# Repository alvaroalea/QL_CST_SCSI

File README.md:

# CST SCSI/FLOPPY CONTROLLER for Sinclar QL

A clone of the CST's Floppy + hardisc Interface for the Sinclair QL

# WARNING: DO NOT USE THIS PROJECT IS NOT TESTED AND MISSING THINGS

An evolution of the CST V4 Floppy interface with the incorporation of SCSI Controller.

The SCSI was limited only to a especific HDD model: Rodine RO652 20Mb, an UK Manufactured HDD that was also used on Macintosh SE

Later this interface will be use as a base for the Thor 20 Computer SCSI interface.

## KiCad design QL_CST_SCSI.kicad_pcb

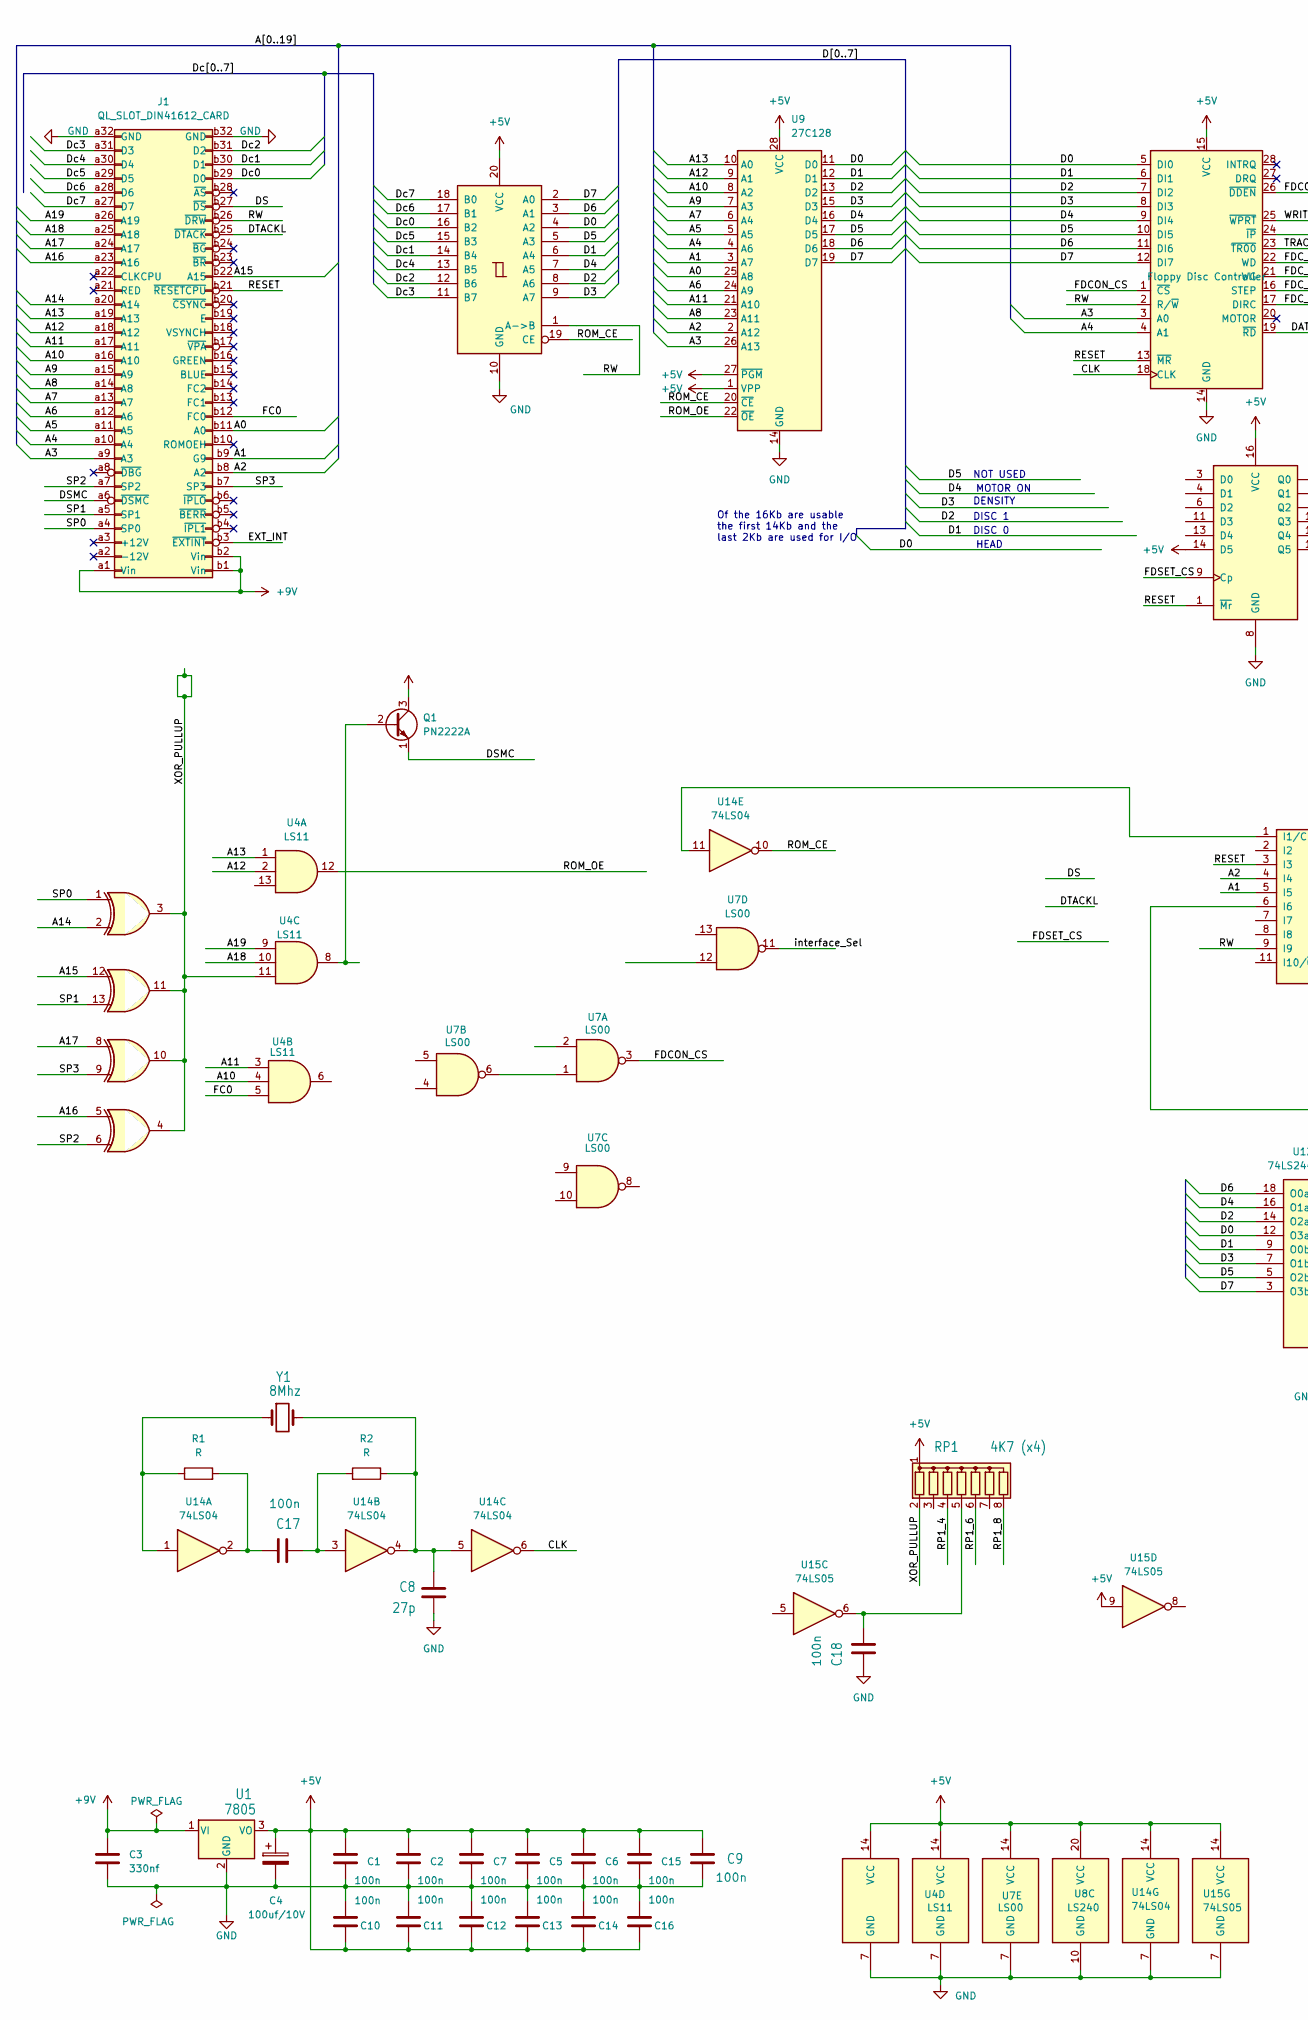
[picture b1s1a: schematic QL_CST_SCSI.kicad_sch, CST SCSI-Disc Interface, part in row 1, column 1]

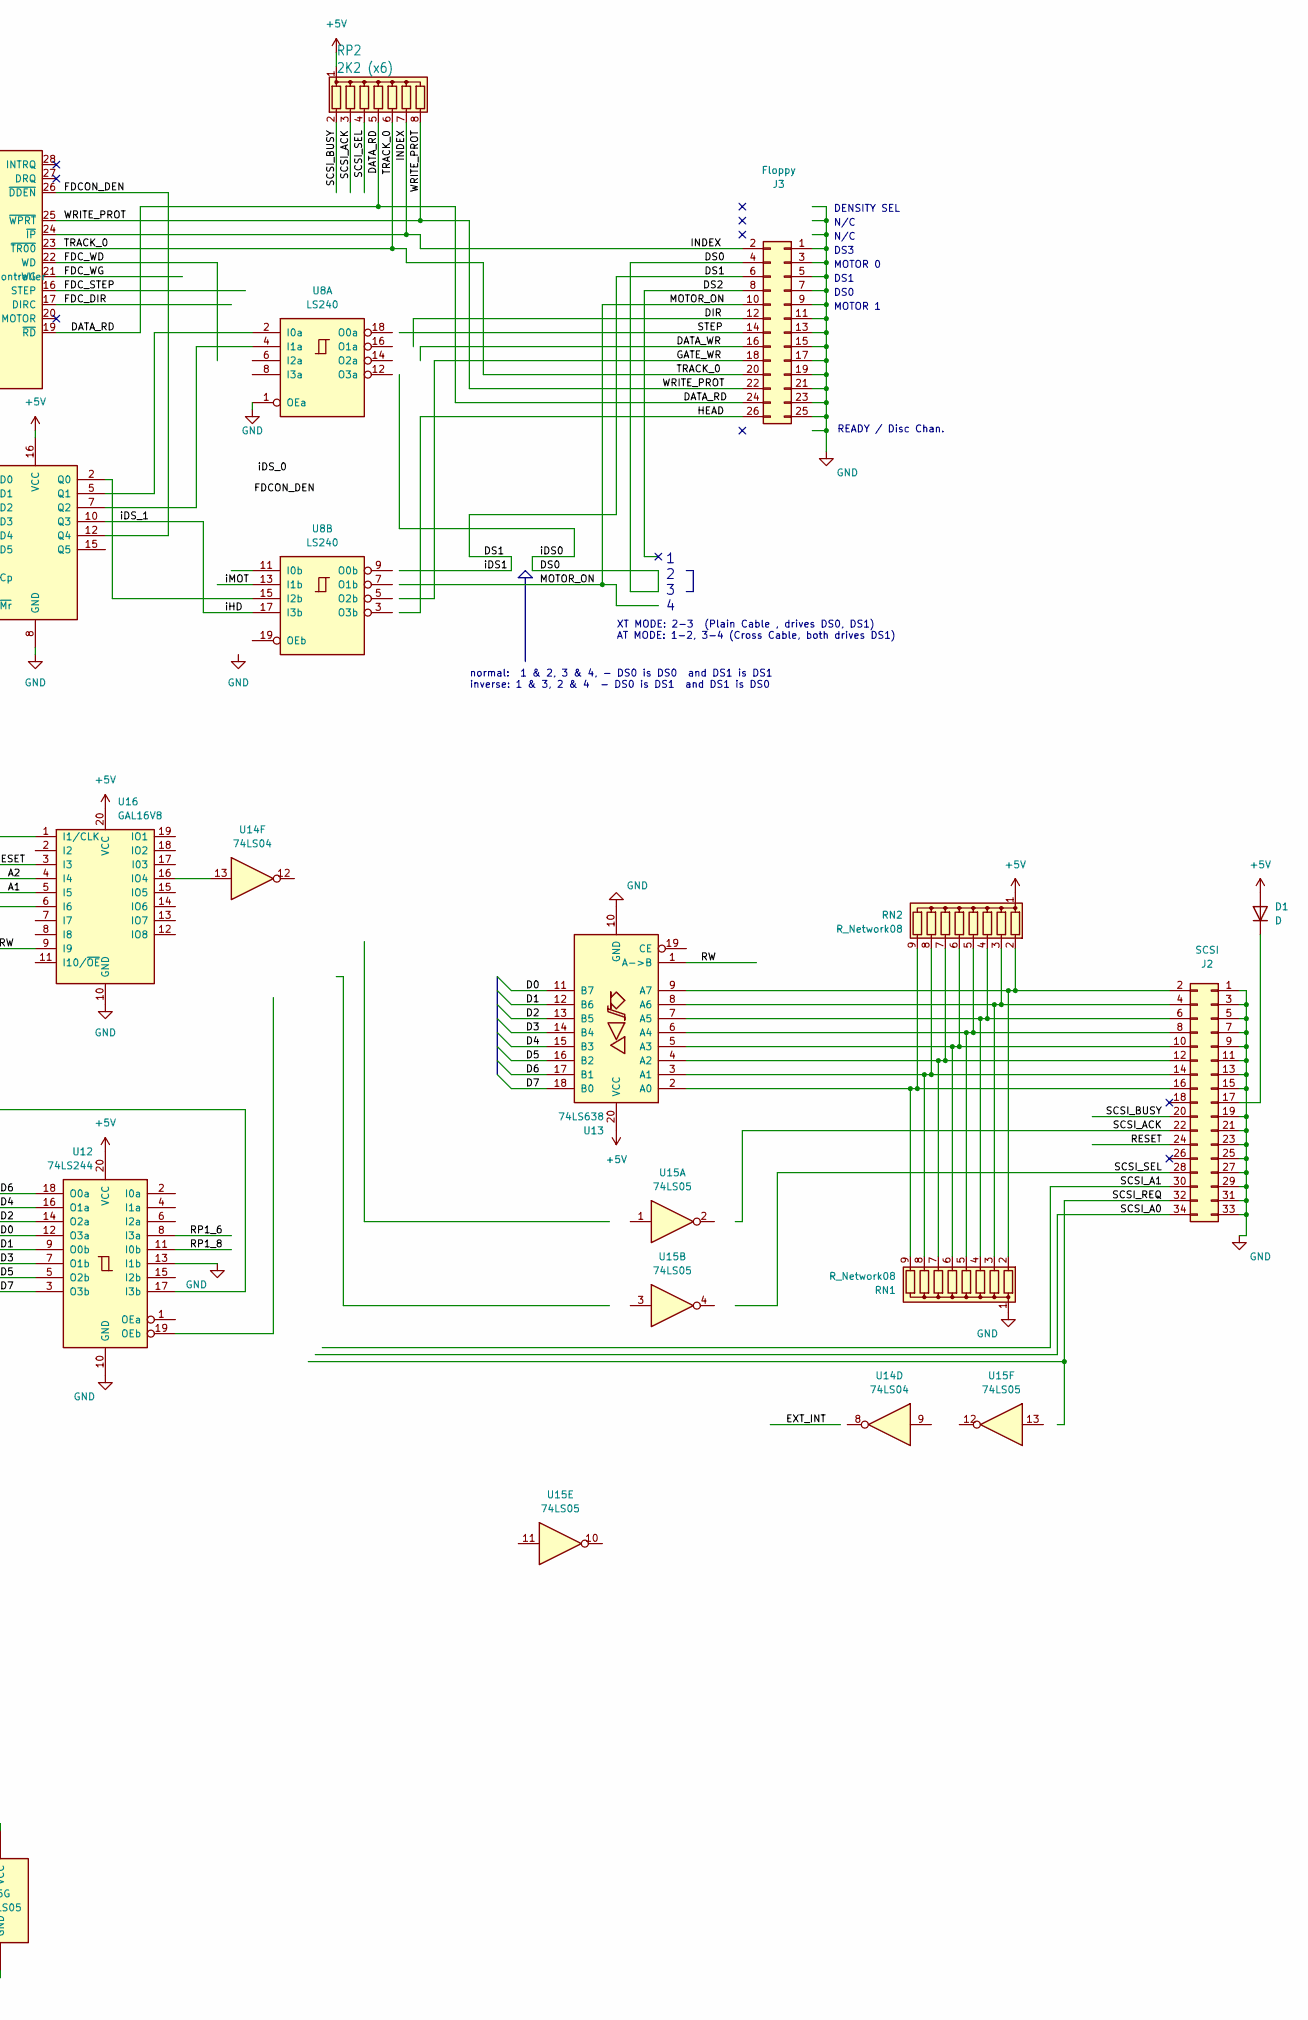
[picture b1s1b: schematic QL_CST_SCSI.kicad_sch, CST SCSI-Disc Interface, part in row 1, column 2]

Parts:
C1, C2, C5, C6, C7, C9, C10, C11, C12, C13, C14, C15, C16, C17, C18: 100n; C_Disc_D7.0mm_W2.5mm_P5.00mm
C3: 330nf; C_Disc_D7.0mm_W2.5mm_P5.00mm
C4: 100uf/10V; CP_Radial_D5.0mm_P2.50mm
C8: 27p; C_Disc_D7.0mm_W2.5mm_P5.00mm
D1: D; D_DO-34_SOD68_P7.62mm_Horizontal
J1: QL_SLOT_DIN41612_CARD; DIN41612_B_2x32_Female_Horizontal_THT
J2: SCSI; PinHeader_2x17_P2.54mm_Vertical
J3: Floppy; PinHeader_2x13_P2.54mm_Vertical
Q1: PN2222A; TO-92S_Wide
R1, R2: R; R_Axial_DIN0207_L6.3mm_D2.5mm_P10.16mm_Horizontal
RN1, RN2: R_Network08; R_Array_SIP9
RP1: 4K7 (x4); R_Array_SIP8
RP2: 2K2 (x6); R_Array_SIP8
U1: 7805; TO-220-3_Horizontal_TabDown
U2: LS266; DIP-14_W7.62mm_Socket
U4: LS11; DIP-14_W7.62mm_Socket
U5: LS245; DIP-20_W7.62mm_Socket
U7: LS00; DIP-14_W7.62mm_Socket
U8: LS240; DIP-20_W7.62mm_Socket
U9: 27C128; DIP-28_W15.24mm_Socket
U10: WD1770; DIP-28_W15.24mm_Socket
U11: LS174; DIP-16_W7.62mm_Socket
U12: 74LS244; DIP-20_W7.62mm_Socket
U13: 74LS638; DIP-20_W7.62mm_Socket
U14: 74LS04; DIP-14_W7.62mm_Socket
U15: 74LS05; DIP-14_W7.62mm_Socket
U16: GAL16V8; DIP-20_W7.62mm_Socket
Y1: 8Mhz; Crystal_HC18-U_Horizontal

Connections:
+5V: C1.1, C2.1, C4.1, C5.1, C6.1, C7.1, C9.2, C10.1, C11.1, C12.1, C13.1, C14.1, C15.1, C16.1, D1.2 (A), Q1.3 (C), RN2.1 (common), RP1.1 (common), RP2.1 (common), U1.3 (VO), U2.14 (VCC), U4.14 (VCC), U5.20 (VCC), U7.14 (VCC), U8.20 (VCC), U9.1 (VPP), U9.27 (~PGM), U9.28 (VCC), U10.15 (VCC), U11.14 (D5), U11.16 (VCC), U12.20 (VCC), U13.20 (VCC), U14.14 (VCC), U15.9, U15.14 (VCC), U16.20 (VCC)
+9V: C3.1, J1.a1 (Vin), J1.b1 (Vin), J1.b2 (Vin), U1.1 (VI)
/A0: J1.b11 (A0), U9.25 (A8)
/A1: J1.b9 (G9), U9.3 (A7), U16.5 (I5)
/A2: J1.b8 (A2), U9.2 (A12), U16.4 (I4)
/A3: J1.a9 (A3), U9.26 (A13), U10.3 (A0)
/A4: J1.a10 (A4), U9.4 (A6), U10.4 (A1)
/A5: J1.a11 (A5), U9.5 (A5)
/A6: J1.a12 (A6), U9.24 (A9)
/A7: J1.a13 (A7), U9.6 (A4)
/A8: J1.a14 (A8), U9.23 (A11)
/A9: J1.a15 (A9), U9.7 (A3)
/A10: J1.a16 (A10), U4.4, U9.8 (A2)
/A11: J1.a17 (A11), U4.3, U9.21 (A10)
/A12: J1.a18 (A12), U4.2, U9.9 (A1)
/A13: J1.a19 (A13), U4.1, U9.10 (A0)
/A14: J1.a20 (A14), U2.2
/A15: J1.b22 (A15), U2.12
/A16: J1.a23 (A16), U2.5
/A17: J1.a24 (A17), U2.8
/A18: J1.a25 (A18), U4.10
/A19: J1.a26 (A19), U4.9
/CLK: U10.18 (CLK), U14.6
/D0: U5.4 (A2), U9.11 (D0), U10.5 (DI0), U12.12 (O3a), U13.11 (B7)
/D1: U5.6 (A4), U9.12 (D1), U10.6 (DI1), U12.9 (O0b), U13.12 (B6)
/D2: U5.8 (A6), U9.13 (D2), U10.7 (DI2), U12.14 (O2a), U13.13 (B5)
/D3: U5.9 (A7), U9.15 (D3), U10.8 (DI3), U12.7 (O1b), U13.14 (B4)
/D4: U5.7 (A5), U9.16 (D4), U10.9 (DI4), U12.16 (O1a), U13.15 (B3)
/D5: U5.5 (A3), U9.17 (D5), U10.10 (DI5), U12.5 (O2b), U13.16 (B2)
/D6: U5.3 (A1), U9.18 (D6), U10.11 (DI6), U12.18 (O0a), U13.17 (B1)
/D7: U5.2 (A0), U9.19 (D7), U10.12 (DI7), U12.3 (O3b), U13.18 (B0)
/DATA_RD: J3.24, RP2.5 (R4), U10.19 (~RD)
/DATA_WR: J3.16
/DIR: J3.12
/DS: J1.b27 (~DS)
/DS0: J3.4
/DS1: J3.6
/DS2: J3.8
/DSMC: J1.a6 (~DSMC), Q1.1 (E)
/DTACKL: J1.b25 (~DTACK)
/Dc0: J1.b29 (D0), U5.16 (B2)
/Dc1: J1.b30 (D1), U5.14 (B4)
/Dc2: J1.b31 (D2), U5.12 (B6)
/Dc3: J1.a31 (D3), U5.11 (B7)
/Dc4: J1.a30 (D4), U5.13 (B5)
/Dc5: J1.a29 (D5), U5.15 (B3)
/Dc6: J1.a28 (D6), U5.17 (B1)
/Dc7: J1.a27 (D7), U5.18 (B0)
/EXT_INT: J1.b3 (~EXTINT)
/FC0: J1.b12 (FC0), U4.5
/FDCON_CS: U7.3, U10.1 (~CS)
/FDCON_DEN: U10.26 (~DDEN), U11.12 (Q4)
/FDC_DIR: U10.17 (DIRC)
/FDC_STEP: U10.16 (STEP)
/FDC_WD: U10.22 (WD)
/FDC_WG: U10.21 (WG)
/FDSET_CS: U11.9 (Cp)
/GATE_WR: J3.18
/HEAD: J3.26
/INDEX: J3.2, RP2.7 (R6), U10.24 (~IP)
/MOTOR_ON: J3.10
/RESET: J1.b21 (~RESETCPU), J2.24, U10.13 (~MR), U11.1 (~Mr), U16.3 (I3)
/ROM_CE: U5.19 (CE), U9.20 (~CE), U14.10
/ROM_OE: U4.12, U9.22 (~OE)
/RP1_4: RP1.4 (R3)
/RP1_6: RP1.6 (R5), U12.8 (I3a)
/RP1_8: RP1.8 (R7), U12.11 (I0b)
/RW: J1.b26 (~DRW), U5.1 (A->B), U10.2 (R/~W), U13.1 (A->B), U16.9 (I9)
/SCSI_A0: J2.34
/SCSI_A1: J2.30
/SCSI_ACK: J2.22, RP2.3 (R2)
/SCSI_BUSY: J2.20, RP2.2 (R1)
/SCSI_REQ: J2.32
/SCSI_SEL: J2.28, RP2.4 (R3)
/SP0: J1.a4 (SP0), U2.1
/SP1: J1.a5 (SP1), U2.13
/SP2: J1.a7 (SP2), U2.6
/SP3: J1.b7 (SP3), U2.9
/STEP: J3.14
/TRACK_0: J3.20, RP2.6 (R5), U10.23 (~TR00)
/WRITE_PROT: J3.22, RP2.8 (R7), U10.25 (~WPRT)
/XOR_PULLUP: RP1.2 (R1), U2.3, U2.4, U2.10, U2.11, U4.11
/iDS_1: U8.17 (I3b), U11.10 (Q3)
/iMOT: U8.13 (I1b)
/interface_Sel: U7.11
GND: C1.2, C2.2, C3.2, C4.2, C5.2, C6.2, C7.2, C8.2, C9.1, C10.2, C11.2, C12.2, C13.2, C14.2, C15.2, C16.2, C18.1, J1.a32 (GND), J1.b32 (GND), J2.1, J2.3, J2.5, J2.7, J2.9, J2.11, J2.13, J2.15, J2.19, J2.21, J2.23, J2.25, J2.27, J2.29, J2.31, J2.33, J3.1, J3.3, J3.5, J3.7, J3.9, J3.11, J3.13, J3.15, J3.17, J3.19, J3.21, J3.23, J3.25, RN1.1 (common), U1.2 (GND), U2.7 (GND), U4.7 (GND), U5.10 (GND), U7.7 (GND), U8.1 (OEa), U8.10 (GND), U9.14 (GND), U10.14 (GND), U11.8 (GND), U12.10 (GND), U12.13 (I1b), U13.10 (GND), U14.7 (GND), U15.7 (GND), U16.10 (GND)
unnamed: C8.1, R2.1, U14.4, U14.5, Y1.2
unnamed: C17.1, R2.2, U14.3
unnamed: C17.2, R1.2, U14.2
unnamed: D1.1 (K), J2.17
unnamed: J2.2, RN1.2 (R1), RN2.2 (R1), U13.9 (A7)
unnamed: J2.4, RN1.3 (R2), RN2.3 (R2), U13.8 (A6)
unnamed: J2.6, RN1.4 (R3), RN2.4 (R3), U13.7 (A5)
unnamed: J2.8, RN1.5 (R4), RN2.5 (R4), U13.6 (A4)
unnamed: J2.10, RN1.6 (R5), RN2.6 (R5), U13.5 (A3)
unnamed: J2.12, RN1.7 (R6), RN2.7 (R6), U13.4 (A2)
unnamed: J2.14, RN1.8 (R7), RN2.8 (R7), U13.3 (A1)
unnamed: J2.16, RN1.9 (R8), RN2.9 (R8), U13.2 (A0)
unnamed: Q1.2 (B), U4.8
unnamed: R1.1, U14.1, Y1.1
unnamed: C18.2, RP1.5 (R4), U15.6
unnamed: U7.1, U7.6
unnamed: U8.15 (I2b), U11.2 (Q0)
unnamed: U8.2 (I0a), U11.5 (Q1)
unnamed: U8.4 (I1a), U11.7 (Q2)
unnamed: U12.17 (I3b), U16.6 (I6)
unnamed: U14.11, U16.1 (I1/CLK)
unnamed: U14.13, U16.16 (IO4)

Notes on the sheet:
XT MODE: 2-3 (Plain Cable , drives DS0, DS1) AT MODE: 1-2, 3-4 (Cross Cable, both drives DS1)
NOT USED
MOTOR ON
MOTOR 0
HEAD
normal: 1 & 2, 3 & 4, - DS0 is DS0 and DS1 is DS1 inverse: 1 & 3, 2 & 4 - DS0 is DS1 and DS1 is DS0
DS0
DS1
READY / Disc Chan.
DENSITY
MOTOR 1
DS3
Of the 16Kb are usable the first 14Kb and the last 2Kb are used for I/O
N/C
1 2 3 4
DISC 1
DENSITY SEL
DISC 0

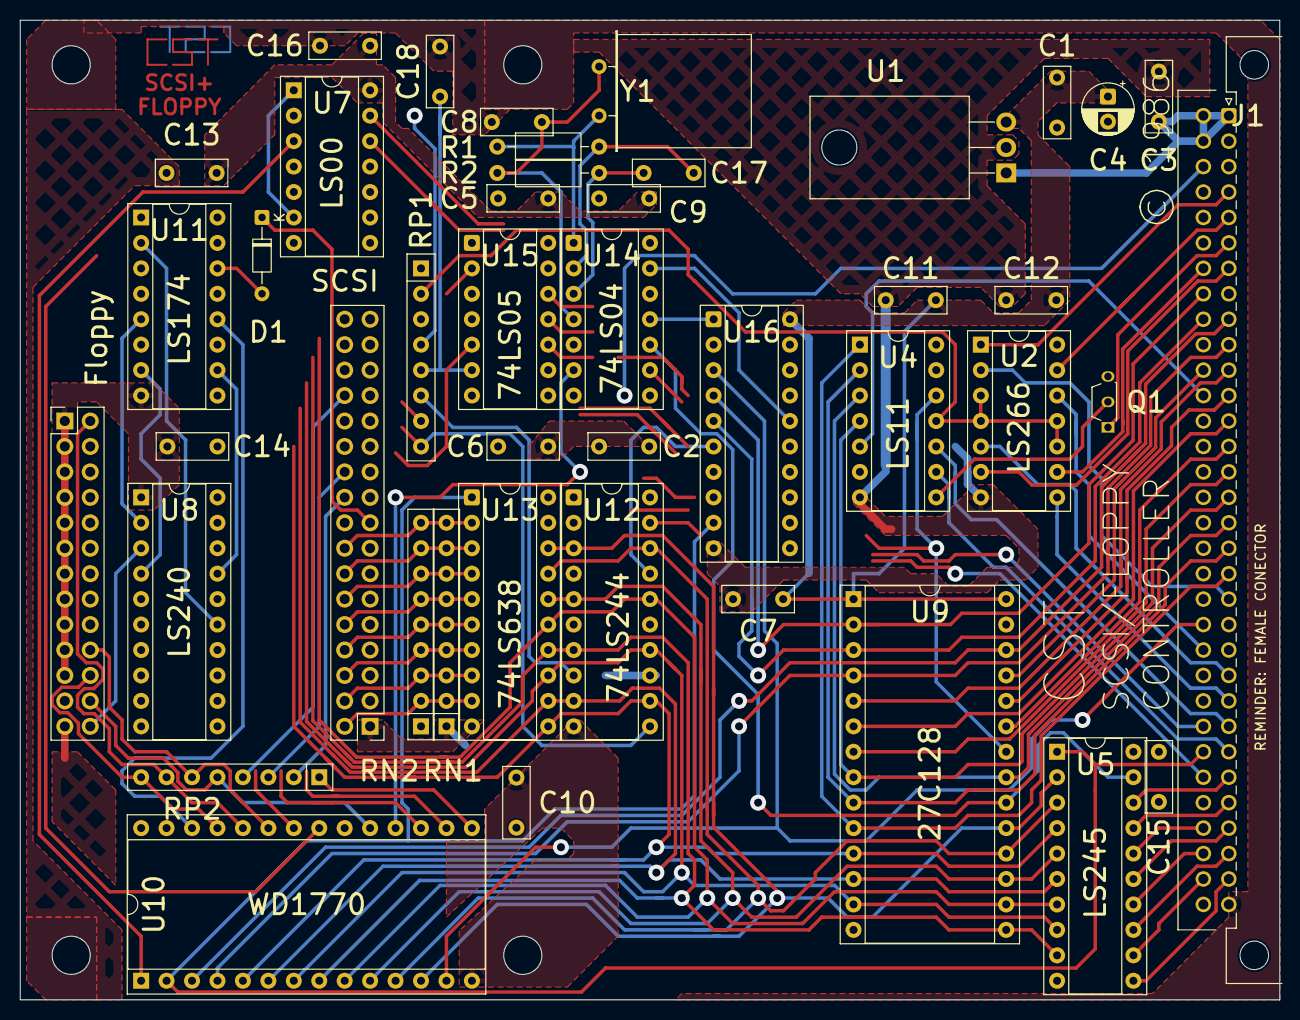
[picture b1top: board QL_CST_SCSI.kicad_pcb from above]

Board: 2 copper layers, 125.7 x 97.8 mm, 44 parts (0 on the bottom side), 85 nets.

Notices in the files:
QL_CST_SCSI.kicad_pcb:
CONTROLLER © 1986
Licensed under Cern OHL-S
